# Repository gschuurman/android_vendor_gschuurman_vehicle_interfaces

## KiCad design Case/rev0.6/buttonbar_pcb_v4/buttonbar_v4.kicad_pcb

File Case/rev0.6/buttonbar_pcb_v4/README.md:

# Button bar PCB v4 (case rev 0.6) - 2026-11-15

One 2-layer board (176.7 x 11.5 mm, 1.6 mm) with everything on it: no hand wiring.
Open `buttonbar_v4.kicad_pro` in KiCad 7-10 (footprints in `buttonbar_v4.pretty`). Gerbers + drill for JLCPCB:
`buttonbar_v4_gerbers.zip`. Status: fully routed, 0 unconnected, 0 copper/clearance errors (only silkscreen
cosmetics in `drc.rpt`). Generated by `scripts/run.sh` (placement in `design.py`, Freerouting).
No schematic sheet yet: the netlist lives in `design.py`.

## What is on it

| Ref | Part | Side | Note |
|---|---|---|---|
| SW1-9 | TC-0120 slim tactile (Glenn's, long plunger) | front | slotted holes 1.9 x 0.9, legs 7.4 apart (6.8-8.0 fits) |
| D1-D10 | SS14 Schottky, SMA | back | stripe (cathode) toward the switch |
| U1 | szfydosh BH1750 module, castellated | front | soldered flat, component side up; ADDR tied to GND (0x23) |
| J1 | JST B5B-PH-K-S (vertical) | back | to main board **J12** pin for pin: 1 screen, 2 vol+, 3 vol-, 4 mute, 5 GND |
| J2 | JST B4B-PH-K-S (vertical) | back | to main board **J7** pin for pin: 1 3V3, 2 GND, 3 SCL, 4 SDA |
| H1-H3 | M3 holes 3.4 | | M3x12 countersunk from the back into M3 inserts in bar_front |
| H4-H5 | 6.6 holes | | the clamp-plate screw ears reach through here (M3x6 countersunk from behind) |

Cables: two straight PH cables (PHR-5 to PHR-5, PHR-4 to PHR-4), pin 1 to pin 1.

Diode coding (unchanged): single buttons pull one J12 line low; combos pull two lines low through SS14s.
Home S+D, Prev D+M, Play U+D, Next U+M, Voice S+U. Firmware decodes the pattern after ~30 ms.

## Check before ordering
- BH1750 pads: 2.54 mm pitch (Glenn confirmed 2026-11-15) along the 11.5 mm edges, centred, castellation centres on the board edge (from the
  datasheet + photos, not measured with calipers). Seen from the component side, left column top to bottom
  NC, GND, ADDR, 3V3; right column SDA, SCL, GND, VCC.
- Board is longer than 100 mm, so it is not the $2 JLCPCB promo: upload the zip at jlcpcb.com/quote for the price.

## Case parts (case/stl/v4_draft, model car_radio_rev06_case.scad with pcb4_data.scad)
Only M3 screws (Glenn 2026-11-15), all countersunk (DIN 7991):

| Where | Screw | Qty | Into |
|---|---|---|---|
| bar_back + PCB -> bar_front | M3x12 | 3 | M3 heat inserts in bar_front (pressed in from the PCB side) |
| cap_plate -> bar_front | M3x6, NOT longer (M3x8 comes through the front) | 2 | straight into the printed pillars (2.5 pilot) |
| bar tongue -> screen tray | M3x6 | 4 | M3 short inserts in the tray: on the printed tray drill the 4 M2 insert holes to 4.0 |

bar_front: M3 bosses 7.6 mm. bar_back: 2.5 mm base, 2 full-length ribs + cross ribs. cap_plate holds the loose caps
(current v3 caps). No JST strap: the headers are soldered to the PCB and the PHR plugs hold by themselves.

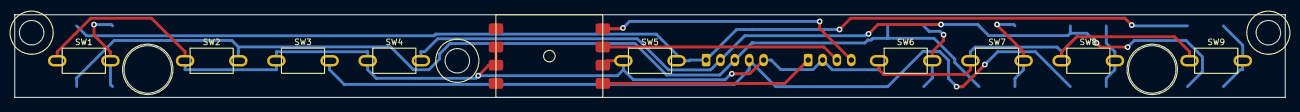
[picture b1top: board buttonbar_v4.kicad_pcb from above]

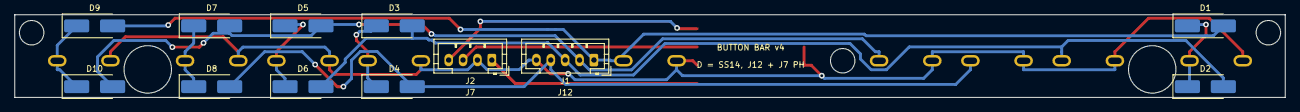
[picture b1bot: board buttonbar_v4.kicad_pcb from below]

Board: 2 copper layers, 176.7 x 11.5 mm, 27 parts (12 on the bottom side), 13 nets.

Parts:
D1, D2, D3, D4, D5, D6, D7, D8, D9, D10: SS14; D_SMA_Handsoldering
H1, H2, H3: M3; MountingHole_3.4mm_M3_NPTH
H4, H5: plate ear; Hole_6.6mm_plate_ear_NPTH
J1: to J12 (B5B-PH-K-S); JST_PH_B5B-PH-K_1x05_P2.00mm_Vertical
J2: to J7 (B4B-PH-K-S); JST_PH_B4B-PH-K_1x04_P2.00mm_Vertical
SW1: Home; SW_TC-0120_2pin_P7.4mm
SW2: Vol -; SW_TC-0120_2pin_P7.4mm
SW3: Mute; SW_TC-0120_2pin_P7.4mm
SW4: Vol +; SW_TC-0120_2pin_P7.4mm
SW5: Screen off; SW_TC-0120_2pin_P7.4mm
SW6: Prev; SW_TC-0120_2pin_P7.4mm
SW7: Play/Pause; SW_TC-0120_2pin_P7.4mm
SW8: Next; SW_TC-0120_2pin_P7.4mm
SW9: Voice; SW_TC-0120_2pin_P7.4mm
U1: BH1750 module (szfydosh); BH1750_szfydosh_castellated

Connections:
/+3V3: J2.1, U1.5
/BTN_MUTE: D4.2, D8.2, J1.4, SW3.2
/BTN_SCREEN: D1.2, D9.2, J1.1, SW5.2
/BTN_VOLDN: D2.2, D3.2, D6.2, J1.3, SW2.2
/BTN_VOLUP: D5.2, D7.2, D10.2, J1.2, SW4.2
/LUX_SCL: J2.3, U1.7
/LUX_SDA: J2.4, U1.8
/N_SW1: D1.1, D2.1, SW1.2
/N_SW6: D3.1, D4.1, SW6.2
/N_SW7: D5.1, D6.1, SW7.2
/N_SW8: D7.1, D8.1, SW8.2
/N_SW9: D9.1, D10.1, SW9.2
GND: J1.5, J2.2, SW1.1, SW2.1, SW3.1, SW4.1, SW5.1, SW6.1, SW7.1, SW8.1, SW9.1, U1.2, U1.3, U1.6

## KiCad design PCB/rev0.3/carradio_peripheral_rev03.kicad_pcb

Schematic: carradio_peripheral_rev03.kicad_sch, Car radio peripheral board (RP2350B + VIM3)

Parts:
C1, C49, C50, C64: 10uF 50V; C_1206_3216Metric; MPN 1206 10uF 50V X5R (Murata GRM31CR61H106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; LCSC C77092
C2, C3, C5, C6, C7, C8, C9, C10, C11, C15, C16, C25, C26, C27, C35, C36, C37, C42, C43, C44, C45, C47, C51, C52, C63, C65, C67, C72, C77, C85, C86, C87, C88, C89, C90, C91, C92, C93, C94, C95, C96, C97, C98, C101, C102, C103: 100nF; C_0603_1608Metric; MPN 0603 100nF 50V X7R; LCSC C14663
C4, C56, C57, C58, C59, C68, C69, C70, C71: 22uF; C_0805_2012Metric; MPN 0805 22uF 25V X5R; LCSC C45783
C12, C13, C18, C19, C20, C21, C24, C34, C61, C66, C75, C80: 1uF; C_0603_1608Metric; MPN 0603 1uF 50V X5R (Murata GRM188R61H105K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; LCSC C77386
C14, C28, C29, C38, C39, C46, C62, C76, C81: 10uF; C_0805_2012Metric; MPN 0805 10uF 25V X5R; LCSC C15850
C17: 10nF; C_0603_1608Metric; MPN 0603 10nF 50V X7R (Samsung CL10B103KB8N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; LCSC C1589
C22, C23, C32, C33: 2.2uF; C_0603_1608Metric; MPN 0603 2.2uF 16V X5R; LCSC C23630
C30, C31, C40, C41: 2.2nF C0G; C_0805_2012Metric; MPN 0805 2.2nF 50V C0G; LCSC C28260
C48: 100uF 50V; CP_Elec_8x10; MPN Panasonic EEEFK1H101P 100uF 50V 8x10.2; LCSC C178548
C53, C82, C83, C84: 4.7uF; C_0603_1608Metric; MPN 0603 4.7uF 16V X5R; LCSC C19666
C54: 4.7nF; C_0603_1608Metric; MPN 0603 4.7nF 50V X7R; LCSC C53987
C55: 22pF; C_0603_1608Metric; MPN 0603 22pF 50V C0G; LCSC C1653
C60: 220uF 10V polymer; CP_Elec_6.3x7.7; MPN Lelon OVZ221M1CTR-0608 polymer 220uF 16V; LCSC C881921
C73, C74: 100uF 6.3V; C_1206_3216Metric; MPN 1206 100uF 6.3V X5R; LCSC C15008
C99, C100: 15pF; C_0603_1608Metric; MPN Samsung CL10C150JB8NNNC 15pF C0G; LCSC C1644
D1, D4, D9: SS34; D_SMA; MPN SS34 40V 3A Schottky; LCSC C8678
D2, D5, D13: SMBJ22A; D_SMB; MPN SMBJ22A (BORN); alt DOWO C284010; LCSC C151920
D6, D7, D11, D12: 1N4148W; D_SOD-123; MPN 1N4148W; LCSC C81598
D8, D15: BZT52C12; D_SOD-123; MPN BZT52C12-7-F 12V zener; LCSC C124196
D10, D16: LED green; LED_0805_2012Metric; MPN KT-0805G green LED; LCSC C2297
D14: Load-dump TVS; D_SMC; MPN Liown 5.0SMDJ22A, 5 kW SMC; LCSC C2990362
F1, F3: PTC 0.5A hold 30V; Fuse_1206_3216Metric; MPN BHFUSE BSMD1206-050-30V; LCSC C883126
F2: PTC 0.75A hold 30V; Fuse_1812_4532Metric; MPN Littelfuse 1812L075/33DR; LCSC C151170
F4: 7.5A fuse; Littelfuse_01530008Z; MPN Littelfuse 01530008Z mini blade holder 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; LCSC C206907
F5: PTC 0.5A; Fuse_1206_3216Metric; MPN Bourns MF-NSMF050-2; LCSC C75464
J1: ISO 10487 A (via pigtail); Molex_Micro-Fit_3.0_43045-0812_2x04_P3.00mm_Vertical; MPN Molex 43045-0812; LCSC C277661
J2: VIM3 40-pin via 2x20 IDC ribbon; IDC-Header_2x20_P2.54mm_Vertical; MPN BOOMELE 2.54-2*20P box header (check it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; LCSC C9138
J5: VIM3 POWER key lead; JST_PH_B2B-PH-K_1x02_P2.00mm_Vertical; MPN JST B2B-PH-K-S; LCSC C131337
J7: BH1750 light sensor; JST_PH_B4B-PH-K_1x04_P2.00mm_Vertical; MPN JST B4B-PH-K-S; LCSC C131334
J8: ISO 10487 C1 (via pigtail); Molex_Micro-Fit_3.0_43045-0612_2x03_P3.00mm_Vertical; MPN Molex 43045-0612; LCSC C234188
J10: Expansion; PinHeader_1x08_P2.54mm_Vertical; MPN Ckmtw B-2100S08P-A110 1x8 male header; LCSC C124381
J11: SMA GNSS antenna; SMA_Amphenol_132289_EdgeMount; MPN Amphenol 132289 SMA edge mount (cheaper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; LCSC C3172723
J12: Display buttons; JST_PH_B5B-PH-K_1x05_P2.00mm_Vertical; MPN JST B5B-PH-K-S; LCSC C157993
J13: HDMI in (from VIM3); HDMI_A_Amphenol_10029449-x01xLF_Horizontal; MPN Amphenol 10029449-111RLF (plating varia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; LCSC C427307
J14: Display FPC 40P 0.5mm; XUNPU_FPC-05FB-40PH20; MPN XUNPU FPC-05FB-40PH20, 40P 0.5mm dual-c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; LCSC C2856837
J17: RTL-SDR (internal); USB_A_Molex_67643_Horizontal; MPN Molex 67643-0910 USB-A; LCSC C2798029
J18: VIM3 VIN (JST-XH 2P); JST_XH_B2B-XH-A_1x02_P2.50mm_Vertical; MPN JST B2B-XH-A; LCSC C158012
J19: External USB 1; USB_A_Molex_67643_Horizontal; MPN Molex 67643-0910 USB-A; LCSC C2798029
J20: External USB 2; USB_A_Molex_67643_Horizontal; MPN Molex 67643-0910 USB-A; LCSC C2798029
J21: Expansion 2; PinHeader_1x10_P2.54mm_Vertical; MPN BOOMELE 1x10 male header 2.54mm; LCSC C57369
J22: SWD; PinHeader_1x04_P2.54mm_Vertical; MPN 1x4 male header 2.54mm; LCSC C124378
JP1: SERVICE jumper; PinHeader_1x02_P2.54mm_Vertical; MPN 1x2 male header 2.54mm + jumper cap C53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; LCSC C124375
L1: 18uH; L_Sunlord_SWPA4030S; MPN SWPA4030S180MT 18uH; LCSC C96895
L2: 27nH RF; L_0402_1005Metric; MPN Murata LQG15HS27NJ02D; LCSC C12669
L3: 4.7uH 12A+; L_Bourns_SRP1245A; MPN Bourns SRP1265A-4R7M 4.7uH Isat 28A 8.4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; LCSC C780205
L4: 8.2uH 5A; L_Coilcraft_XAL6060-XXX; MPN Coilcraft XAL6060-822MEC 8.2uH Isat 8.4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; LCSC C19191627
L5: 3.3uH; L_Murata_DFE201610P; MPN Abracon AOTA-B201610S3R3-101-T 3.3uH (R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; LCSC C42411119
NT1, NT2, NT3: NetTie; NetTie-2_SMD_Pad0.5mm; MPN net tie (copper only, not a part)
Q1: AO3400A; SOT-23; MPN AO3400A 30V 5.7A N-MOSFET; LCSC C20917
Q2: P-MOSFET -60V; SOT-23; MPN onsemi FDN5618P -60V P-MOSFET (check 1=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; LCSC C400792
Q3: 2N7002; SOT-23; MPN JSCJ 2N7002; LCSC C8545
Q10: P-MOSFET -40V; TO-252-2; MPN NCE40P70K -40V 10 mOhm P-MOSFET TO-252 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; LCSC C130101
Q11, Q12: CSD18543Q3A; VSON-8_3.3x3.3mm_P0.65mm_NexFET; MPN TI CSD18543Q3A 60V 8.5mOhm N-MOSFET; LCSC C840100
R1, R15, R19, R35, R70, R72, R75, R96: 100k; R_0603_1608Metric; MPN 0603 100k 1%; LCSC C25803
R2, R76: 24k; R_0603_1608Metric; MPN 0603 24k 1%; LCSC C23352
R3, R5, R29, R31: 4.7kΩ 0805; R_0805_2012Metric; MPN 0805 4.7k 1%; LCSC C17673
R4, R6, R8, R9, R18, R30, R32, R33, R34, R94, R95: 4.7k; R_0603_1608Metric; MPN 0603 4.7k 1%; LCSC C23162
R7, R37, R38, R39, R40, R46, R59, R61, R63, R65, R73, R79, R81, R82, R86, R90: 1k; R_0603_1608Metric; MPN 0603 1k 1%; LCSC C21190
R10: 1M; R_0603_1608Metric; MPN 0603 1M 1%; LCSC C22935
R11: 220k; R_0603_1608Metric; MPN 0603 220k 1%; LCSC C22961
R12, R16, R23, R24: 100Ω; R_0603_1608Metric; MPN 0603 100 1%; LCSC C22775
R13, R14, R47, R58, R60, R62, R64, R66, R85, R87, R88, R89, R91, R92, R93: 10k; R_0603_1608Metric; MPN 0603 10k 1%; LCSC C25804
R41: 10Ω; R_0603_1608Metric; MPN 0603 10 1%; LCSC C22859
R42, R43, R44, R45, R80: 33Ω; R_0603_1608Metric; MPN 0603 33 1%; LCSC C23140
R48, R49, R50, R51: 470Ω; R_0603_1608Metric; MPN 0603 470 1%; LCSC C23179
R56, R67: 0Ω; R_0603_1608Metric; MPN 0603 0 1%; LCSC C21189
R57: 0Ω; R_0603_1608Metric; MPN 0603 0 1%; LCSC C21189; not fitted
R68: 47k; R_0603_1608Metric; MPN 0603 47k 1% (YAGEO RC0603FR-0747KL); LCSC C105579
R69: 30k; R_0603_1608Metric; MPN UNI-ROYAL 0603WAF3002T5E; LCSC C22984
R71: 8.2k; R_0603_1608Metric; MPN 0603 8.2k 1%; LCSC C25981
R74: 10mΩ 2512; R_2512_6332Metric; MPN Yageo PA2512FKE7T0R01E 10 mOhm 1% 3W; LCSC C375691
R77: 39k; R_0603_1608Metric; MPN 0603 39k 1%; LCSC C23153
R83, R84: 27Ω; R_0603_1608Metric; MPN UNI-ROYAL 0603WAF270JT5E 27R; LCSC C25190
SW1: BOOTSEL; SW_SPST_TL3342; MPN E-Switch TL3342F160QG; LCSC C2886898
SW2: RESET; SW_SPST_TL3342; MPN E-Switch TL3342F160QG; LCSC C2886898
TH1: NTC 10k B3950; R_0603_1608Metric; MPN Murata NCP18XH103F03RB 10k B3380 0603; LCSC C13564
U1: TPS560430XDBVR; SOT-23-6; MPN TPS560430XDBVR 36V 600mA buck, 1.1MHz; LCSC C524782
U2, U3, U4, U5: EL817S1(C); SMDIP-4_W7.62mm; MPN EL817S1(C)(TU)-F (EL817S1(C)(TU)-FV); LCSC C470884
U6, U8, U9: LP5907MFX-3.3; SOT-23-5; MPN TI LP5907MFX-3.3/NOPB 250mA LDO (TECH P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; LCSC C5370990
U7: NEO-M9N-00B; ublox_NEO; MPN u-blox NEO-M9N-00B; LCSC C5119087
U10, U11: PCM5102APWR; TSSOP-20_4.4x6.5mm_P0.65mm; MPN TI PCM5102APWR 32-bit 384kHz stereo DAC; LCSC C107671
U12: TPS55288RPMR; TPS55288RPMR_VQFN-HR-26; MPN TI TPS55288RPMR; LCSC C2864583
U13, U14: CH334R; QSOP-16_3.9x4.9mm_P0.635mm; MPN WCH CH334R 4-port USB 2.0 hub, QSOP-16; LCSC C4154405
U15: LMR33630ADDA; TI_SO-PowerPAD-8_ThermalVias; MPN TI LMR33630ADDAR 36V 3A buck, 400 kHz; LCSC C841384
U16: TPS2561DRCR; VSON-10-1EP_3x3mm_P0.5mm_EP1.65x2.4mm; MPN TI TPS2561DRCR dual 2.8A USB power swit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; LCSC C140303
U17, U18: USBLC6-2SC6; SOT-23-6; MPN ST USBLC6-2SC6; LCSC C7519
U19: AP2112K-3.3; SOT-23-5; MPN Diodes AP2112K-3.3TRG1; LCSC C51118
U20: RP2350B; QFN-80-1EP_10x10mm_P0.4mm_EP3.4x3.4mm; MPN Raspberry Pi RP2350B QFN-80 (LCSC stock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; LCSC C42415655
U21: W25Q128JVS; SOIC-8_5.3x5.3mm_P1.27mm; MPN Winbond W25Q128JVSIQ; LCSC C97521
Y1, Y2: 12MHz; Crystal_SMD_3225-4Pin_3.2x2.5mm; MPN YXC X322512MSB4SI 12MHz; LCSC C9002
Y3: 12MHz; Crystal_SMD_3225-4Pin_3.2x2.5mm; MPN Abracon ABM8-272-T3 12MHz (Raspberry Pi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; LCSC C20625731

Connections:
/+1V1_MCU: C83.1, C93.1, C94.1, C95.1, L5.2, U20.10 (DVDD), U20.32 (DVDD), U20.51 (DVDD), U20.65 (VREG_FB)
/+3V3_DAC_A: C19.1, C25.1, C26.1, C28.1, C35.1, C36.1, C38.1, U8.5 (OUT), U10.1 (CPVDD), U10.8 (AVDD), U11.1 (CPVDD), U11.8 (AVDD)
/+3V3_DAC_D: C21.1, C27.1, C29.1, C37.1, C39.1, U9.5 (OUT), U10.20 (DVDD), U11.20 (DVDD)
/+3V3_GNSS: C13.1, C14.1, C15.1, U6.5 (OUT), U7.23 (VCC)
/+3V3_MCU: C8.1, C16.1, C81.1, C82.1, C85.1, C86.1, C87.1, C88.1, C89.1, C90.1, C91.1, C92.1, C96.1, C97.1, C98.1, J7.1, J10.1, J21.1, JP1.1, R33.1, R34.1, R58.1, R60.1, R62.1, R64.1, R80.1, R85.1, R87.1, R88.1, R89.1, R93.1, U2.4, U3.4, U4.4, U5.4, U7.22 (V_BCKP), U19.5 (VOUT), U20.5 (IOVDD), U20.15 (IOVDD), U20.24 (IOVDD), U20.29 (IOVDD), U20.41 (IOVDD), U20.50 (IOVDD), U20.59 (ADC_AVDD), U20.60 (IOVDD), U20.64 (VREG_VIN), U20.68 (USB_OTP_VDD), U20.69 (QSPI_IOVDD), U20.76 (IOVDD), U21.8 (VCC)
/+5V_AON: C4.1, C12.1, C80.1, J10.5, L1.2, R1.1, U6.1 (IN), U19.1 (VIN), U19.3 (EN)
/+5V_SYS: C46.1, C47.1, C61.1, C75.1, F5.1, J14.4, J14.5, J14.6, J18.1, NT2.2, R74.2, R91.1, U13.12 (V5), U14.12 (V5)
/+5V_USB: C68.1, C69.1, C70.1, C71.1, C72.1, L4.2, R75.1, U16.2 (IN), U16.3 (IN), U16.4 (EN1), U16.5 (EN2)
/ACC_F: D4.2 (A), F2.2
/ACC_LED: D6.1 (K), R3.2, U2.1
/ACC_P: C5.1, D4.1 (K), D5.1 (K), D8.1 (K), Q2.2 (S), R3.1, R13.1, R31.1
/ACC_RAW: F2.1, J1.7
/AMP_CTRL: Q3.1 (G), R15.1, R16.2
/AMP_G: D8.2 (A), Q2.1 (G), R13.2, R14.1
/AMP_LED: D10.2 (A), R18.2
/AMP_PULL: Q3.3 (D), R14.2
/AMP_REM: D9.1 (K), D13.1 (K), F3.2, J1.3, J8.6, R18.1, R57.1
/AMP_SW: F3.1, Q2.3 (D)
/ANT_FEED: L2.1, R41.2
/BATT_F: D1.2 (A), F1.2
/BATT_F2: F4.2, Q10.2 (D)
/BATT_RAW: F1.1, F4.1, J1.4
/BB_AGND: C54.2, C55.2, NT3.1, R67.2, R68.2, R69.2, R70.2, U12.7 (DITH/SYNC), U12.10 (AGND)
/BB_BOOT1: C51.1, U12.22 (BOOT1)
/BB_BOOT2: C52.1, U12.20 (BOOT2)
/BB_CDC: R70.1, U12.16 (CDC)
/BB_COMP: C55.1, R71.1, U12.18 (COMP)
/BB_COMP_RC: C54.1, R71.2
/BB_FSW: R68.1, U12.8 (FSW)
/BB_ILIM: R69.1, U12.17 (ILIM)
/BB_ISN: NT2.1, U12.13 (ISN)
/BB_ISP: NT1.1, U12.12 (ISP)
/BB_MODE: R67.1, U12.15 (MODE)
/BB_SW1: C51.2, L3.1, Q11.1 (S), Q11.2 (S), Q11.3 (S), Q12.5 (D), U12.23 (SW1); also elsewhere on the board
/BB_SW2: C52.2, L3.2, U12.21 (SW2), U12.25 (SW2)
/BB_VCC: C53.1, U12.19 (VCC)
/BB_VOUT: C56.1, C57.1, C58.1, C59.1, C60.1, NT1.2, R74.1, U12.11 (VOUT), U12.26 (VOUT)
/BL_EN: J14.37, R23.2
/BL_PWM: J14.36, R24.2
/BOOTSEL_SW: R81.2, SW1.1
/BTN_MUTE: J12.4, R65.1
/BTN_SCREEN: J12.1, R59.1
/BTN_VOLDN: J12.3, R63.1
/BTN_VOLUP: J12.2, R61.1
/BUCK_CB: C3.1, U1.1 (CB)
/BUCK_FB: R1.2, R2.1, U1.3 (FB)
/BUCK_SW: C3.2, L1.1, U1.6 (SW)
/DAC_FL: R48.1, U10.6 (OUTL)
/DAC_FR: R49.1, U10.7 (OUTR)
/DAC_RL: R50.1, U11.6 (OUTL)
/DAC_RR: R51.1, U11.7 (OUTR)
/DAC_XSMT: R46.2, R47.1, U10.17 (XSMT), U11.17 (XSMT)
/EXP_GP20: J10.2, U20.20 (GPIO20)
/EXP_GP21: J10.3, U20.21 (GPIO21)
/EXP_GP30: J10.4, U20.38 (GPIO30)
/EXP_GP31: J10.8, U20.39 (GPIO31)
/EXP_GP32: J21.2, U20.40 (GPIO32)
/EXP_GP33: J21.3, U20.42 (GPIO33)
/EXP_GP34: J21.4, U20.43 (GPIO34)
/EXP_GP35: J21.5, U20.44 (GPIO35)
/EXP_GP36: J21.6, U20.45 (GPIO36)
/EXP_GP37: J21.7, U20.46 (GPIO37)
/EXP_GP38: J21.8, U20.47 (GPIO38)
/EXP_GP39: J21.9, U20.48 (GPIO39)
/EXT1_DM: J19.2 (D-), U14.7 (DM1-), U17.3 (I/O2), U17.4 (I/O2)
/EXT1_DP: J19.3 (D+), U14.8 (DP1+), U17.1 (I/O1), U17.6 (I/O1)
/EXT1_VBUS: C73.1, J19.1 (VBUS), U16.9 (OUT1), U17.5 (VBUS)
/EXT2_DM: J20.2 (D-), U14.5 (DM2-), U18.3 (I/O2), U18.4 (I/O2)
/EXT2_DP: J20.3 (D+), U14.6 (DP2+), U18.1 (I/O1), U18.6 (I/O1)
/EXT2_VBUS: C74.1, J20.1 (VBUS), U16.8 (OUT2), U18.5 (VBUS)
/GNSS_PPS: R40.1, U7.3 (TIMEPULSE)
/GNSS_RF: J11.1 (In), L2.2, U7.11 (RF_IN)
/GNSS_RST: R39.2, U7.8 (~RESET)
/GNSS_RXD: R37.2, U7.21 (RXD/SPI_MOSI)
/GNSS_SAFEBOOT: R79.2, U7.1 (~SAFEBOOT)
/GNSS_TXD: R38.1, U7.20 (TXD/SPI_MISO)
/GNSS_VCCRF: C17.1, R41.1, U7.9 (VCC_RF)
/HDMI_5V: J13.18 (+5V), J14.27
/HDMI_CEC: J13.13 (CEC), J14.23
/HDMI_CLKN: J13.12 (CK-), J14.22
/HDMI_CLKP: J13.10 (CK+), J14.20
/HDMI_D0N: J13.9 (D0-), J14.19
/HDMI_D0P: J13.7 (D0+), J14.17
/HDMI_D1N: J13.6 (D1-), J14.16
/HDMI_D1P: J13.4 (D1+), J14.14
/HDMI_D2N: J13.3 (D2-), J14.13
/HDMI_D2P: J13.1 (D2+), J14.11
/HDMI_HPD: J13.19 (HPD), J14.28
/HDMI_SCL: J13.15 (SCL), J14.24
/HDMI_SDA: J13.16 (SDA), J14.25
/HUB1_RST: R90.2, U13.9 (~RESET/CDP)
/HUB2_3V3: C76.1, C77.1, U14.9 (~RESET/CDP), U14.13 (VDD33)
/HUB2_UP_DM: U13.1 (DM4-), U14.10 (DMU-)
/HUB2_UP_DP: U13.2 (DP4+), U14.11 (DPU+)
/HUB2_XI: U14.16 (XI), Y2.1
/HUB2_XO: U14.15 (XO), Y2.3
/HUB_3V3: C62.1, C63.1, U13.13 (VDD33)
/HUB_XI: U13.16 (XI), Y1.1
/HUB_XO: U13.15 (XO), Y1.3
/I2S_BCLK: R42.2, U10.13 (BCK), U11.13 (BCK)
/I2S_DOUT0: R44.2, U10.14 (DIN)
/I2S_DOUT1: R45.2, U11.14 (DIN)
/I2S_LRCK: R43.2, U10.15 (LRCK), U11.15 (LRCK)
/ILLUM_LED: D7.1 (K), R5.2, U3.1
/ILLUM_RAW: J1.6, R5.1
/ISO_A5: J1.5, R57.2
/LINE_FL: C30.1, J8.3, R48.2
/LINE_FR: C31.1, J8.4, R49.2
/LINE_GND: J8.5, R56.1
/LINE_RL: C40.1, J8.1, R50.2
/LINE_RR: C41.1, J8.2, R51.2
/LUX_SCL: J7.3, R33.2, U12.5 (SCL), U20.2 (GPIO5)
/LUX_SDA: J7.4, R34.2, U12.6 (SDA), U20.1 (GPIO4)
/MCU_5VSYS_ADC: C102.1, R91.2, R92.1, U20.52 (GPIO41/ADC1)
/MCU_ACC_IN: C6.1, R4.1, U2.3, U20.79 (GPIO2)
/MCU_AMP_EN: R16.1, U20.7 (GPIO9)
/MCU_BL_EN: R23.1, R96.1, U20.8 (GPIO10)
/MCU_BL_PWM: R24.1, U20.9 (GPIO11)
/MCU_BTN_MUTE: C45.1, R64.2, R65.2, U20.28 (GPIO27)
/MCU_BTN_SCREEN: C42.1, R58.2, R59.2, U20.16 (GPIO16)
/MCU_BTN_VOLDN: C44.1, R62.2, R63.2, U20.22 (GPIO22)
/MCU_BTN_VOLUP: C43.1, R60.2, R61.2, U20.17 (GPIO17)
/MCU_DAC_MUTE: R46.1, U20.14 (GPIO15)
/MCU_GNSS_EN: R35.1, U6.3 (EN), U20.11 (GPIO12)
/MCU_GNSS_PPS: R40.2, R94.1, U20.19 (GPIO19)
/MCU_GNSS_RST: R39.1, U20.18 (GPIO18)
/MCU_GNSS_RX: R38.2, R95.1, U20.78 (GPIO1)
/MCU_GNSS_SAFEBOOT: R79.1, U20.37 (GPIO29)
/MCU_GNSS_TX: R37.1, U20.77 (GPIO0)
/MCU_HUB_RST: R90.1, U20.54 (GPIO43/ADC3)
/MCU_ILLUM_IN: C7.1, R6.1, U3.3, U20.3 (GPIO6)
/MCU_LED: R86.1, U20.26 (GPIO25)
/MCU_LED_K: D16.2 (A), R86.2
/MCU_PARK_IN: C11.1, R32.1, U5.3, U20.4 (GPIO7)
/MCU_PWR_KEY: R12.1, U20.6 (GPIO8)
/MCU_REV_IN: C10.1, R30.1, U4.3, U20.80 (GPIO3)
/MCU_RUN: C101.1, J22.4, R85.2, SW2.1, U20.35 (RUN)
/MCU_SBC_SENSE: R7.2, R8.1, U20.12 (GPIO13)
/MCU_SERVICE: JP1.2, R9.1, U20.13 (GPIO14)
/MCU_SWCLK: J22.1, U20.33 (SWCLK)
/MCU_SWDIO: J22.3, U20.34 (SWDIO)
/MCU_TEMP_ADC: C103.1, R93.2, TH1.1, U20.53 (GPIO42/ADC2)
/MCU_USBP_FAULT1: R87.2, U16.10 (~FAULT1), U20.23 (GPIO23)
/MCU_USBP_FAULT2: R88.2, U16.6 (~FAULT2), U20.25 (GPIO24)
/MCU_USBP_PG: R89.2, U15.4 (PG), U20.27 (GPIO26)
/MCU_USB_DM: R83.2, U13.7 (DM1-)
/MCU_USB_DM_R: R83.1, U20.66 (USB_DM)
/MCU_USB_DP: R84.2, U13.8 (DP1+)
/MCU_USB_DP_R: R84.1, U20.67 (USB_DP)
/MCU_VBAT_ADC: C9.1, R10.2, R11.1, U20.49 (GPIO40/ADC0)
/MCU_VIM3_PWR_EN: R73.1, U20.36 (GPIO28)
/MCU_VREG_AVDD: C84.1, R80.2, U20.61 (VREG_AVDD)
/MCU_VREG_LX: L5.1, U20.63 (VREG_LX)
/MCU_XIN: C99.1, U20.30 (XIN), Y3.1
/MCU_XOUT: R82.1, U20.31 (XOUT)
/MCU_XTAL_R: C100.1, R82.2, Y3.3
/PARK_K: D12.2 (A), U5.2
/PARK_LED: R31.2, U5.1
/PARK_RAW: D12.1 (K), J1.2
/PWR_KEY_G: Q1.1 (G), R12.2, R19.1
/QSPI_SCLK: U20.71 (QSPI_SCLK), U21.6 (CLK)
/QSPI_SD0: U20.72 (QSPI_SD0), U21.5 (DI(IO0))
/QSPI_SD1: U20.74 (QSPI_SD1), U21.2 (DO(IO1))
/QSPI_SD2: U20.73 (QSPI_SD2), U21.3 (IO2)
/QSPI_SD3: U20.70 (QSPI_SD3), U21.7 (IO3)
/QSPI_SS: R81.1, U20.75 (~QSPI_SS), U21.1 (~CS)
/REV_LED: D11.1 (K), R29.2, U4.1
/REV_RAW: J1.1, R29.1
/RPP_G: D15.2 (A), Q10.1 (G), R66.1
/SDR_DM: J17.2 (D-), U13.3 (DM3-)
/SDR_DP: J17.3 (D+), U13.4 (DP3+)
/SDR_VBUS: F5.2, J17.1 (VBUS)
/TOUCH_DN: J14.34, U13.5 (DM2-)
/TOUCH_DP: J14.33, U13.6 (DP2+)
/U10_CAPM: C22.2, U10.4 (CAPM)
/U10_CAPP: C22.1, U10.2 (CAPP)
/U10_LDOO: C24.1, U10.18 (LDOO)
/U10_VNEG: C23.1, U10.5 (VNEG)
/U11_CAPM: C32.2, U11.4 (CAPM)
/U11_CAPP: C32.1, U11.2 (CAPP)
/U11_LDOO: C34.1, U11.18 (LDOO)
/U11_VNEG: C33.1, U11.5 (VNEG)
/USBP_BOOT: C67.1, U15.7 (BOOT)
/USBP_FB: R75.2, R76.1, U15.5 (FB)
/USBP_ILIM: R77.1, U16.7 (ILM)
/USBP_SW: C67.2, L4.1, U15.8 (SW)
/USBP_VCC: C66.1, U15.6 (VCC)
/USB_UP_DM: J2.5 (V3:USB_DM), U13.10 (DMU-)
/USB_UP_DP: J2.7 (V4:USB_DP), U13.11 (DPU+)
/VBAT_P: C1.1, C2.1, D1.1 (K), D2.1 (K), R10.1, U1.4 (EN), U1.5 (VIN)
/VIM3_3V3: J2.14 (V27:3V3), J2.39 (V20:3V3), R7.1
/VIM3_5V: C18.1, C20.1, J2.1 (V1:5V), J2.3 (V2:5V), U8.1 (IN), U8.3 (EN), U9.1 (IN), U9.3 (EN)
/VIM3_I2S_BCLK: J2.18 (V29:TDMB_SCLK), R42.1
/VIM3_I2S_DOUT0: J2.22 (V31:TDMB_DOUT0), R44.1
/VIM3_I2S_DOUT1: J2.26 (V33:TDMB_DOUT1), R45.1
/VIM3_I2S_LRCK: J2.24 (V32:TDMB_FS), R43.1
/VIM3_PWR_EN: R72.1, R73.2, U12.4 (EN/UVLO), U15.3 (EN)
/VIM3_PWR_KEY: J5.1, Q1.3 (D)
/VSYS_IN: C48.1, C49.1, C50.1, C64.1, C65.1, D14.1 (K), D15.1 (K), Q10.3 (S), Q11.5 (D), U12.3 (VIN), U15.2 (VIN)
GND: C1.2, C2.2, C4.2, C5.2, C6.2, C7.2, C8.2, C9.2, C10.2, C11.2, C12.2, C13.2, C14.2, C15.2, C16.2, C17.2, C18.2, C19.2, C20.2, C21.2, C23.2, C24.2, C25.2, C26.2, C27.2, C28.2, C29.2, C30.2, C31.2, C33.2, C34.2, C35.2, C36.2, C37.2, C38.2, C39.2, C40.2, C41.2, C42.2, C43.2, C44.2, C45.2, C46.2, C47.2, C48.2, C49.2, C50.2, C53.2, C56.2, C57.2, C58.2, C59.2, C60.2, C61.2, C62.2, C63.2, C64.2, C65.2, C66.2, C68.2, C69.2, C70.2, C71.2, C72.2, C73.2, C74.2, C75.2, C76.2, C77.2, C80.2, C81.2, C82.2, C83.2, C84.2, C85.2, C86.2, C87.2, C88.2, C89.2, C90.2, C91.2, C92.2, C93.2, C94.2, C95.2, C96.2, C97.2, C98.2, C99.2, C100.2, C101.2, C102.2, C103.2, D2.2 (A), D5.2 (A), D6.2 (A), D7.2 (A), D9.2 (A), D10.1 (K), D11.2 (A), D13.2 (A), D14.2 (A), D16.1 (K), J1.8, J2.2 (V21:GND), J2.8 (V24:GND), J2.9 (V5:GND), J2.16 (V28:GND), J2.17 (V9:GND), J2.27 (V14:GND), J2.28 (V34:GND), J2.33 (V17:GND), J2.40 (V40:GND), J5.2, J7.2, J10.6, J10.7, J11.2 (Ext), J12.5, J13.2 (D2S), J13.5 (D1S), J13.8 (D0S), J13.11 (CKS), J13.17 (GND), J13.SH, J14.8, J14.9, J14.10, J14.12, J14.15, J14.18, J14.21, J14.26, J14.35, J14.MP (MountPin), J17.4 (GND), J17.SH (Shield), J18.2, J19.4 (GND), J19.SH (Shield), J20.4 (GND), J20.SH (Shield), J21.10, J22.2, NT3.2, Q1.2 (S), Q3.2 (S), Q12.1 (S), Q12.2 (S), Q12.3 (S), R2.2, R4.2, R6.2, R8.2, R9.2, R11.2, R15.2, R19.2, R30.2, R32.2, R35.2, R47.2, R56.2, R66.2, R72.2, R76.2, R77.2, R92.2, R94.2, R95.2, R96.2, SW1.2, SW2.2, TH1.2, U1.2 (GND), U2.2, U3.2, U4.2, U6.2 (GND), U7.7 (VDD_USB), U7.10 (GND), U7.12 (GND), U7.13 (GND), U7.24 (GND), U8.2 (GND), U9.2 (GND), U10.3 (CPGND), U10.9 (AGND), U10.10 (DEMP), U10.11 (FLT), U10.12 (SCK), U10.16 (FMT), U10.19 (DGND), U11.3 (CPGND), U11.9 (AGND), U11.10 (DEMP), U11.11 (FLT), U11.12 (SCK), U11.16 (FMT), U11.19 (DGND), U12.9 (PGND), U12.24 (PGND), U13.14 (GND), U14.14 (GND), U15.1 (GND), U15.9 (GND), U16.1 (GND), U16.11 (PAD), U17.2 (GND), U18.2 (GND), U19.2 (GND), U20.62 (VREG_PGND), U20.81 (GND (pad)), U21.4 (GND), Y1.2, Y1.4, Y2.2, Y2.4, Y3.2, Y3.4; also elsewhere on the board

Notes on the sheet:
1. ISO 10487 CONNECTOR A (power) + ALWAYS-ON 5V FOR PICO AND GNSS
J1 pad n = ISO A pin n. A1 REVERSE A2 HANDBRAKE A3 AMP REMOTE A4 BATT+ A5 remote (R57) A6 ILLUM A7 ACC A8 GND
Always-on 5.2V: MCU VSYS + GNSS LDO. TPS560430X runs PFM at light load (~55uA Iq).
2. VEHICLE INPUTS (opto-isolated). ACC, ILLUM, REVERSE: +12V = on. PARK: switch to ground = on.
ACC (ISO A7)
ILLUM (ISO A6)
REVERSE lamp (ISO A1)
PARK (ISO A2, handbrake switch; may stay unwired)
LED ~2.7mA at 14.4V; EL817 C-grade CTR >= 200%. 4.7k pull-downs satisfy RP2350-E9.
3. AMPLIFIER REMOTE (+12V from ACC, MCU GP9)
Goes to ISO A3 and C1-6 (A5 via R57). ~1A capable; remote inputs draw <100mA.
Only works while ACC is on, even if the MCU hangs.
4. MCU HELPERS (MCU core is section 13)
GPIO map: see section 13 and DESIGN_rev03.md.
5. GNSS: u-blox NEO-M9N, active antenna on SMA
Active antenna (3.3V): VCC_RF -> 10R -> 27nH onto RF_IN. RF_IN is DC-blocked inside the module (verify in the integration manual).
6. VIM3 POWER KEY, BACKLIGHT, LIGHT SENSOR (all from the MCU)
Backlight and reverse moved off the VIM3 header; the VHAL now sets/reads them through the MCU.
Display buttons (to GND): GP16 screen, GP17 vol+, GP22 vol-, GP27 mute. J12.
7. AUDIO: VIM3 TDM-B I2S -> 2x PCM5102A (front + rear) -> line out on ISO C1
I2S series resistors at the ribbon entry.
2.1 Vrms ground-centred line out, no coupling caps. 24-bit in 32-bit I2S slots, 48/96/192 kHz.
8. VIM3 40-PIN HEADER + ISO 10487 C1 (line out)
VIM3 pin v -> IDC pad 2v-1 (v<=20) or 2(v-20) (v>20). Pin 1 sits opposite pin 21 (confirmed by Glenn).
Pin 35 (TDM-B lane 3) left free for a later sub/3rd pair. MCLK (30) not used.
J8 pad n = ISO C1 pin n: 1 RL, 2 RR, 3 FL, 4 FR, 5 line GND, 6 remote +12V.
9. DISPLAY: Waveshare 7in 70H-1024600 adapter built in (HDMI in from VIM3 -> 40-pin FPC to the panel)
Panel 5V (~0.45A) comes from the board's switched 5V rail (+5V_SYS, section 10), not from VIM3 USB. Touch USB goes to the on-board hub (section 11).
Backlight EN/PWM now go straight to the panel: 0V = brightest, 3.3V = darkest (invert PWM in firmware). J6 removed.
FPC orientation as on the Waveshare adapter: seen from the top, ribbon leaving the board edge, pin 1 is on the RIGHT, pin 40 on the left.
10. 5V/5A SYSTEM SUPPLY FOR VIM3 + SCREEN + HUB (TPS55288 buck-boost, rides through cranking and overvoltage)
Input 3V-36V (runs through cranking); output 5.0V up to 5A. MCU GP28 = EN, MCU I2C0 sets OE/voltage/current limit.
VIN is permanent +12V so the VIM3 can finish its Android shutdown after ACC drops.
11. USB HUB: VIM3 header USB (pins 3/4) -> MCU, screen touch, spare port
One link to the VIM3: no USB cables. Port 1 MCU (HID + GNSS CDC), 2 touch, 3 RTL-SDR, 4 second hub (external ports). Route D+/D- as 90 ohm pairs.
VIM3 header pins 3/4 are a working USB host port (confirmed by Glenn, 2026-09-29).
12. EXTERNAL USB PORTS (phone etc.): second hub + dedicated 5V/3A supply, 1.5A current-limited per port
Ports are powered only while the VIM3 supply is on. All USB shares the VIM3 header's USB 2.0 link (480 Mbit/s); RTL-SDR needs ~40 Mbit/s.
13. MCU: RP2350B (QFN-80) + 16MB QSPI flash + 12MHz crystal + 3.3V LDO, per the Raspberry Pi Pico 2 reference design
GPIO0-29 as rev 0.2 except: GPIO40 battery ADC (was GP26), GPIO23/24 USB port faults, GPIO25 LED, GPIO26 USB supply PG,

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
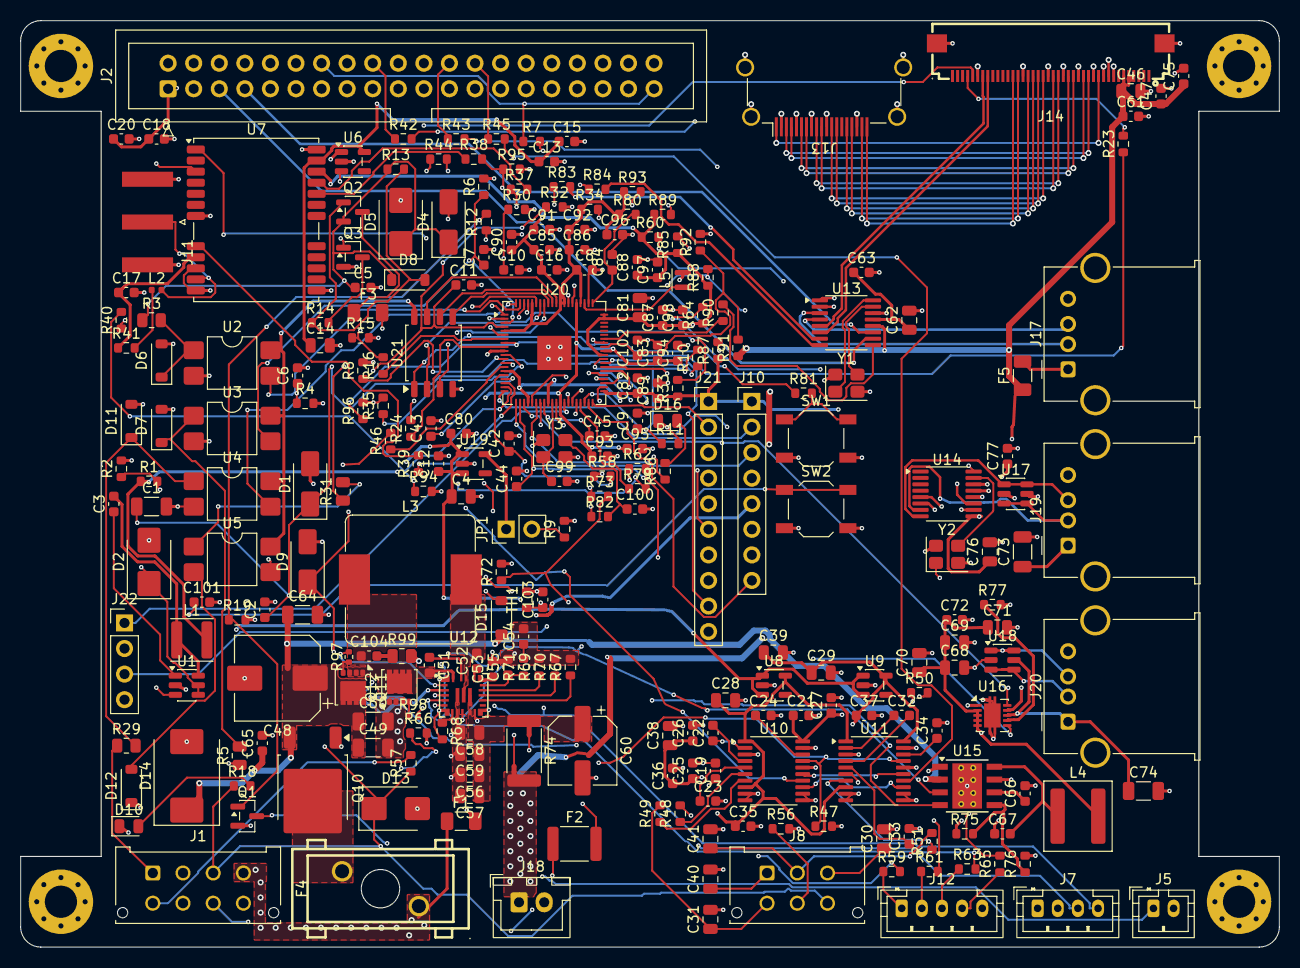
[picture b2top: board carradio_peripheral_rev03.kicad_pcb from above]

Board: 4 copper layers, 125.0 x 92.0 mm, 269 parts (0 on the bottom side), 205 nets.

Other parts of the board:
C104: 1nF; C_0603_1608Metric
H1, H2, H3, H4: M3; MountingHole_3.2mm_M3_Pad_Via
R97, R98: 0Ω; R_0402_1005Metric
R99: 2.2Ω 0805; R_0805_2012Metric

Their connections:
/BB_SNUB: C104.2, R99.1
/BB_SW1: C104.1; also elsewhere on the board
GND: H1.1, H2.1, H3.1, H4.1, R99.2; also elsewhere on the board

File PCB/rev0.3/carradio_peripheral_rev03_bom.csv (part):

Designator,Value,Description / MPN,LCSC,Footprint (KiCad name),Fit,Note
J1,ISO 10487 A (via pigtail),Molex 43045-0812,C277661,Connector_Molex:Molex_Micro-Fit_3.0_43045-0812_2x04_P3.00mm_Vertical,yes,"pad n = ISO A pin n: A1 reverse lamp, A2 handbrake switch, A3 amp remote out, A4 +12V permanent, A5 remote (via R57), A6 illumination, A7 ACC, A8 GND"
F1,PTC 0.5A hold 30V,BHFUSE BSMD1206-050-30V,C883126,Fuse:Fuse_1206_3216Metric,yes,
D1,SS34,SS34 40V 3A Schottky,C8678,Diode_SMD:D_SMA,yes,reverse-polarity protection
D2,SMBJ22A,SMBJ22A (BORN); alt DOWO C284010,C151920,Diode_SMD:D_SMB,yes,review 2026-09-29: 22V standoff survives a 24V jump start; 35.5V max clamp stays under the 38V limit of the TPS560430 and LMR33630
C1,10uF 50V,1206 10uF 50V X5R (Murata GRM31CR61H106KA12L),C77092,Capacitor_SMD:C_1206_3216Metric,yes,
C2,100nF,0603 100nF 50V X7R,C14663,Capacitor_SMD:C_0603_1608Metric,yes,
U1,TPS560430XDBVR,"TPS560430XDBVR 36V 600mA buck, 1.1MHz",C524782,Package_TO_SOT_SMD:SOT-23-6,yes,pinout checked against TI datasheet
C3,100nF,0603 100nF 50V X7R,C14663,Capacitor_SMD:C_0603_1608Metric,yes,
L1,18uH,SWPA4030S180MT 18uH,C96895,Inductor_SMD:L_Sunlord_SWPA4030S,yes,
R1,100k,0603 100k 1%,C25803,Resistor_SMD:R_0603_1608Metric,yes,
R2,24k,0603 24k 1%,C23352,Resistor_SMD:R_0603_1608Metric,yes,Vout = 1.0V x (1 + 100k/24k) = 5.17V
C4,22uF,0805 22uF 25V X5R,C45783,Capacitor_SMD:C_0805_2012Metric,yes,
F2,PTC 0.75A hold 30V,Littelfuse 1812L075/33DR,C151170,Fuse:Fuse_1812_4532Metric,yes,
D4,SS34,SS34 40V 3A Schottky,C8678,Diode_SMD:D_SMA,yes,
D5,SMBJ22A,SMBJ22A (BORN); alt DOWO C284010,C151920,Diode_SMD:D_SMB,yes,review 2026-09-29: 22V standoff survives a 24V jump start; 35.5V max clamp stays under the 38V limit of the TPS560430 and LMR33630
C5,100nF,0603 100nF 50V X7R,C14663,Capacitor_SMD:C_0603_1608Metric,yes,
R3,4.7kΩ 0805,0805 4.7k 1%,C17673,Resistor_SMD:R_0805_2012Metric,yes,
D6,1N4148W,1N4148W,C81598,Diode_SMD:D_SOD-123,yes,reverse-voltage clamp across opto LED
U2,EL817S1(C),EL817S1(C)(TU)-F (EL817S1(C)(TU)-FV),C470884,Package_DIP:SMDIP-4_W7.62mm,yes,
R4,4.7k,0603 4.7k 1%,C23162,Resistor_SMD:R_0603_1608Metric,yes,
C6,100nF,0603 100nF 50V X7R,C14663,Capacitor_SMD:C_0603_1608Metric,yes,
R5,4.7kΩ 0805,0805 4.7k 1%,C17673,Resistor_SMD:R_0805_2012Metric,yes,
D7,1N4148W,1N4148W,C81598,Diode_SMD:D_SOD-123,yes,reverse-voltage clamp across opto LED
U3,EL817S1(C),EL817S1(C)(TU)-F (EL817S1(C)(TU)-FV),C470884,Package_DIP:SMDIP-4_W7.62mm,yes,
R6,4.7k,0603 4.7k 1%,C23162,Resistor_SMD:R_0603_1608Metric,yes,
C7,100nF,0603 100nF 50V X7R,C14663,Capacitor_SMD:C_0603_1608Metric,yes,
R29,4.7kΩ 0805,0805 4.7k 1%,C17673,Resistor_SMD:R_0805_2012Metric,yes,
D11,1N4148W,1N4148W,C81598,Diode_SMD:D_SOD-123,yes,reverse-voltage clamp across opto LED
U4,EL817S1(C),EL817S1(C)(TU)-F (EL817S1(C)(TU)-FV),C470884,Package_DIP:SMDIP-4_W7.62mm,yes,
R30,4.7k,0603 4.7k 1%,C23162,Resistor_SMD:R_0603_1608Metric,yes,
C10,100nF,0603 100nF 50V X7R,C14663,Capacitor_SMD:C_0603_1608Metric,yes,
R31,4.7kΩ 0805,0805 4.7k 1%,C17673,Resistor_SMD:R_0805_2012Metric,yes,"PARK input: LED fed from ACC, handbrake switch pulls cathode to ground"
U5,EL817S1(C),EL817S1(C)(TU)-F (EL817S1(C)(TU)-FV),C470884,Package_DIP:SMDIP-4_W7.62mm,yes,
D12,1N4148W,1N4148W,C81598,Diode_SMD:D_SOD-123,yes,series diode: blocks reverse voltage when ACC is off
R32,4.7k,0603 4.7k 1%,C23162,Resistor_SMD:R_0603_1608Metric,yes,
C11,100nF,0603 100nF 50V X7R,C14663,Capacitor_SMD:C_0603_1608Metric,yes,
C8,100nF,0603 100nF 50V X7R,C14663,Capacitor_SMD:C_0603_1608Metric,yes,
R57,0Ω,0603 0 1%,C21189,Resistor_SMD:R_0603_1608Metric,DNP,DNP: fit to also put the amp remote on ISO A5 (the usual antenna/amp remote pin)
Q2,P-MOSFET -60V,onsemi FDN5618P -60V P-MOSFET (check 1=G 2=S 3=D in datasheet),C400792,Package_TO_SOT_SMD:SOT-23,yes,review: AO3401A (-30V) was below the 35.5V TVS clamp
R13,10k,0603 10k 1%,C25804,Resistor_SMD:R_0603_1608Metric,yes,
D8,BZT52C12,BZT52C12-7-F 12V zener,C124196,Diode_SMD:D_SOD-123,yes,Vgs clamp
R14,10k,0603 10k 1%,C25804,Resistor_SMD:R_0603_1608Metric,yes,
Q3,2N7002,JSCJ 2N7002,C8545,Package_TO_SOT_SMD:SOT-23,yes,"review: drain sees ACC through R13, so it needs more than 30V"
R16,100Ω,0603 100 1%,C22775,Resistor_SMD:R_0603_1608Metric,yes,
R15,100k,0603 100k 1%,C25803,Resistor_SMD:R_0603_1608Metric,yes,amp off while the MCU is in reset
F3,PTC 0.5A hold 30V,BHFUSE BSMD1206-050-30V,C883126,Fuse:Fuse_1206_3216Metric,yes,own fuse: a shorted remote wire cannot pull down ACC
D9,SS34,SS34 40V 3A Schottky,C8678,Diode_SMD:D_SMA,yes,clamps inductive kick from the remote wire
D13,SMBJ22A,SMBJ22A (BORN); alt DOWO C284010,C151920,Diode_SMD:D_SMB,yes,review 2026-09-29: 22V standoff survives a 24V jump start; 35.5V max clamp stays under the 38V limit of the TPS560430 and LMR33630
R18,4.7k,0603 4.7k 1%,C23162,Resistor_SMD:R_0603_1608Metric,yes,
D10,LED green,KT-0805G green LED,C2297,LED_SMD:LED_0805_2012Metric,yes,amp remote on
R7,1k,0603 1k 1%,C21190,Resistor_SMD:R_0603_1608Metric,yes,VIM3 on/off sense
R8,4.7k,0603 4.7k 1%,C23162,Resistor_SMD:R_0603_1608Metric,yes,
R10,1M,0603 1M 1%,C22935,Resistor_SMD:R_0603_1608Metric,yes,battery sense: 14.4V -> 2.6V
R11,220k,0603 220k 1%,C22961,Resistor_SMD:R_0603_1608Metric,yes,
C9,100nF,0603 100nF 50V X7R,C14663,Capacitor_SMD:C_0603_1608Metric,yes,
JP1,SERVICE jumper,1x2 male header 2.54mm + jumper cap C5305,C124375,Connector_PinHeader_2.54mm:PinHeader_1x02_P2.54mm_Vertical,yes,
R9,4.7k,0603 4.7k 1%,C23162,Resistor_SMD:R_0603_1608Metric,yes,
J10,Expansion,Ckmtw B-2100S08P-A110 1x8 male header,C124381,Connector_PinHeader_2.54mm:PinHeader_1x08_P2.54mm_Vertical,yes,GP20/21 = UART1 for a future K-line (L9637D) board; pins 4/8 = spare GP30/GP31
U6,LP5907MFX-3.3,TI LP5907MFX-3.3/NOPB 250mA LDO (TECH PUBLIC TPLP5907MFX-3.3 clone; TI part out of stock at LCSC),C5370990,Package_TO_SOT_SMD:SOT-23-5,yes,"GNSS supply, switched by MCU GP12"
C12,1uF,0603 1uF 50V X5R (Murata GRM188R61H105KAALD),C77386,Capacitor_SMD:C_0603_1608Metric,yes,
R35,100k,0603 100k 1%,C25803,Resistor_SMD:R_0603_1608Metric,yes,GNSS off by default
C13,1uF,0603 1uF 50V X5R (Murata GRM188R61H105KAALD),C77386,Capacitor_SMD:C_0603_1608Metric,yes,
C14,10uF,0805 10uF 25V X5R,C15850,Capacitor_SMD:C_0805_2012Metric,yes,
C15,100nF,0603 100nF 50V X7R,C14663,Capacitor_SMD:C_0603_1608Metric,yes,
C16,100nF,0603 100nF 50V X7R,C14663,Capacitor_SMD:C_0603_1608Metric,yes,at V_BCKP
U7,NEO-M9N-00B,u-blox NEO-M9N-00B,C5119087,RF_GPS:ublox_NEO,yes,V_BCKP from always-on 3V3 for hot starts. V_USB tied to GND (USB unused). SAFEBOOT_N driven by MCU GPIO29 through R79 (recovery only).
R37,1k,0603 1k 1%,C21190,Resistor_SMD:R_0603_1608Metric,yes,
R38,1k,0603 1k 1%,C21190,Resistor_SMD:R_0603_1608Metric,yes,
R39,1k,0603 1k 1%,C21190,Resistor_SMD:R_0603_1608Metric,yes,firmware drives low only to reset
R40,1k,0603 1k 1%,C21190,Resistor_SMD:R_0603_1608Metric,yes,
C17,10nF,0603 10nF 50V X7R (Samsung CL10B103KB8NNNC),C1589,Capacitor_SMD:C_0603_1608Metric,yes,
R41,10Ω,0603 10 1%,C22859,Resistor_SMD:R_0603_1608Metric,yes,"antenna supply, limits short-circuit current"
L2,27nH RF,Murata LQG15HS27NJ02D,C12669,Inductor_SMD:L_0402_1005Metric,yes,"RF choke: feeds DC to the antenna, blocks GNSS signal"
J11,SMA GNSS antenna,"Amphenol 132289 SMA edge mount (cheaper: XUNPU C5723200, check pads)",C3172723,Connector_Coaxial:SMA_Amphenol_132289_EdgeMount,yes,"50 ohm coplanar trace to RF_IN, as short as possible"
Q1,AO3400A,AO3400A 30V 5.7A N-MOSFET,C20917,Package_TO_SOT_SMD:SOT-23,yes,open-drain press of the active-low VIM3 POWER key (GPIOAO_7)
R12,100Ω,0603 100 1%,C22775,Resistor_SMD:R_0603_1608Metric,yes,
R19,100k,0603 100k 1%,C25803,Resistor_SMD:R_0603_1608Metric,yes,
J5,VIM3 POWER key lead,JST B2B-PH-K-S,C131337,Connector_JST:JST_PH_B2B-PH-K_1x02_P2.00mm_Vertical,yes,wire to the VIM3 power-key pad
R23,100Ω,0603 100 1%,C22775,Resistor_SMD:R_0603_1608Metric,yes,
R24,100Ω,0603 100 1%,C22775,Resistor_SMD:R_0603_1608Metric,yes,
R33,4.7k,0603 4.7k 1%,C23162,Resistor_SMD:R_0603_1608Metric,yes,
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
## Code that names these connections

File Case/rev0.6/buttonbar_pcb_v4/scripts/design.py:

# Button bar v4 (2026-11-15): one 2-layer PCB, switches + SS14 diodes + BH1750 module + 2x JST PH.
# Coordinates: x from bar centre (front view, = KiCad top view), y from the PCB top edge downward.
L, H = 176.7, 11.5
SW_Y = 6.4                  # switch row (cap centre), 0.65 below the board centre
YC = H / 2
D_UP, D_DN = 1.55, 10.0     # SS14 rows on the back, above / below the switch row
LINES = {"S": "/BTN_SCREEN", "U": "/BTN_VOLUP", "D": "/BTN_VOLDN", "M": "/BTN_MUTE"}
BTNS = [("SW1", "Home",       -78.74, "SD"),
        ("SW2", "Vol -",      -60.96, "D"),
        ("SW3", "Mute",       -48.26, "M"),
        ("SW4", "Vol +",      -35.56, "U"),
        ("SW5", "Screen off",   0.00, "S"),
        ("SW6", "Prev",        35.56, "DM"),
        ("SW7", "Play/Pause",  48.26, "UD"),
        ("SW8", "Next",        60.96, "UM"),
        ("SW9", "Voice",       78.74, "SU")]
D_SHIFT = {"SW1": 1.5, "SW9": -1.5}       # keep the end diodes clear of the M3 standoffs
BH_X = -14.0                # BH1750 module centre (light window in the bar)
J1_X, J2_X = 7.8, 22.0      # pin 1 x of the JST headers (back side): J1 -> main board J12, J2 -> J7
J_Y = YC + 0.55             # pin row so the 4.5 mm housing is centred on the board
HOLES = [(-86.0, 2.5), (-26.8, SW_Y), (86.0, 2.5)]   # M3 countersunk (ends above the switch row: clear of the home/voice legs)
J1_PINS = ["/BTN_SCREEN", "/BTN_VOLUP", "/BTN_VOLDN", "/BTN_MUTE", "GND"]   # = J12 pin 1..5
J2_PINS = ["/+3V3", "GND", "/LUX_SCL", "/LUX_SDA"]                            # = J7 pin 1..4
BH_PINS = {"1": None, "2": "GND", "3": "GND", "4": None,                      # 3V3 out (NC), ADDR->GND, GND, NC
           "5": "/+3V3", "6": "GND", "7": "/LUX_SCL", "8": "/LUX_SDA"}        # VCC, GND, SCL, SDA
def node(ref): return "/N_" + ref
def diodes():
    out = []; n = 1
    for ref, lab, x, ls in BTNS:
        if len(ls) == 2:
            for l, y in zip(ls, (D_UP, D_DN)):
                out.append(("D%d" % n, x + D_SHIFT.get(ref, 0), y, LINES[l], node(ref), lab)); n += 1
    return out
HEAD_HOLES = [(-69.85, 7.6), (69.85, 7.6)]   # 6.6 holes: the cap-plate screw ears (M3 countersunk) reach through the PCB
